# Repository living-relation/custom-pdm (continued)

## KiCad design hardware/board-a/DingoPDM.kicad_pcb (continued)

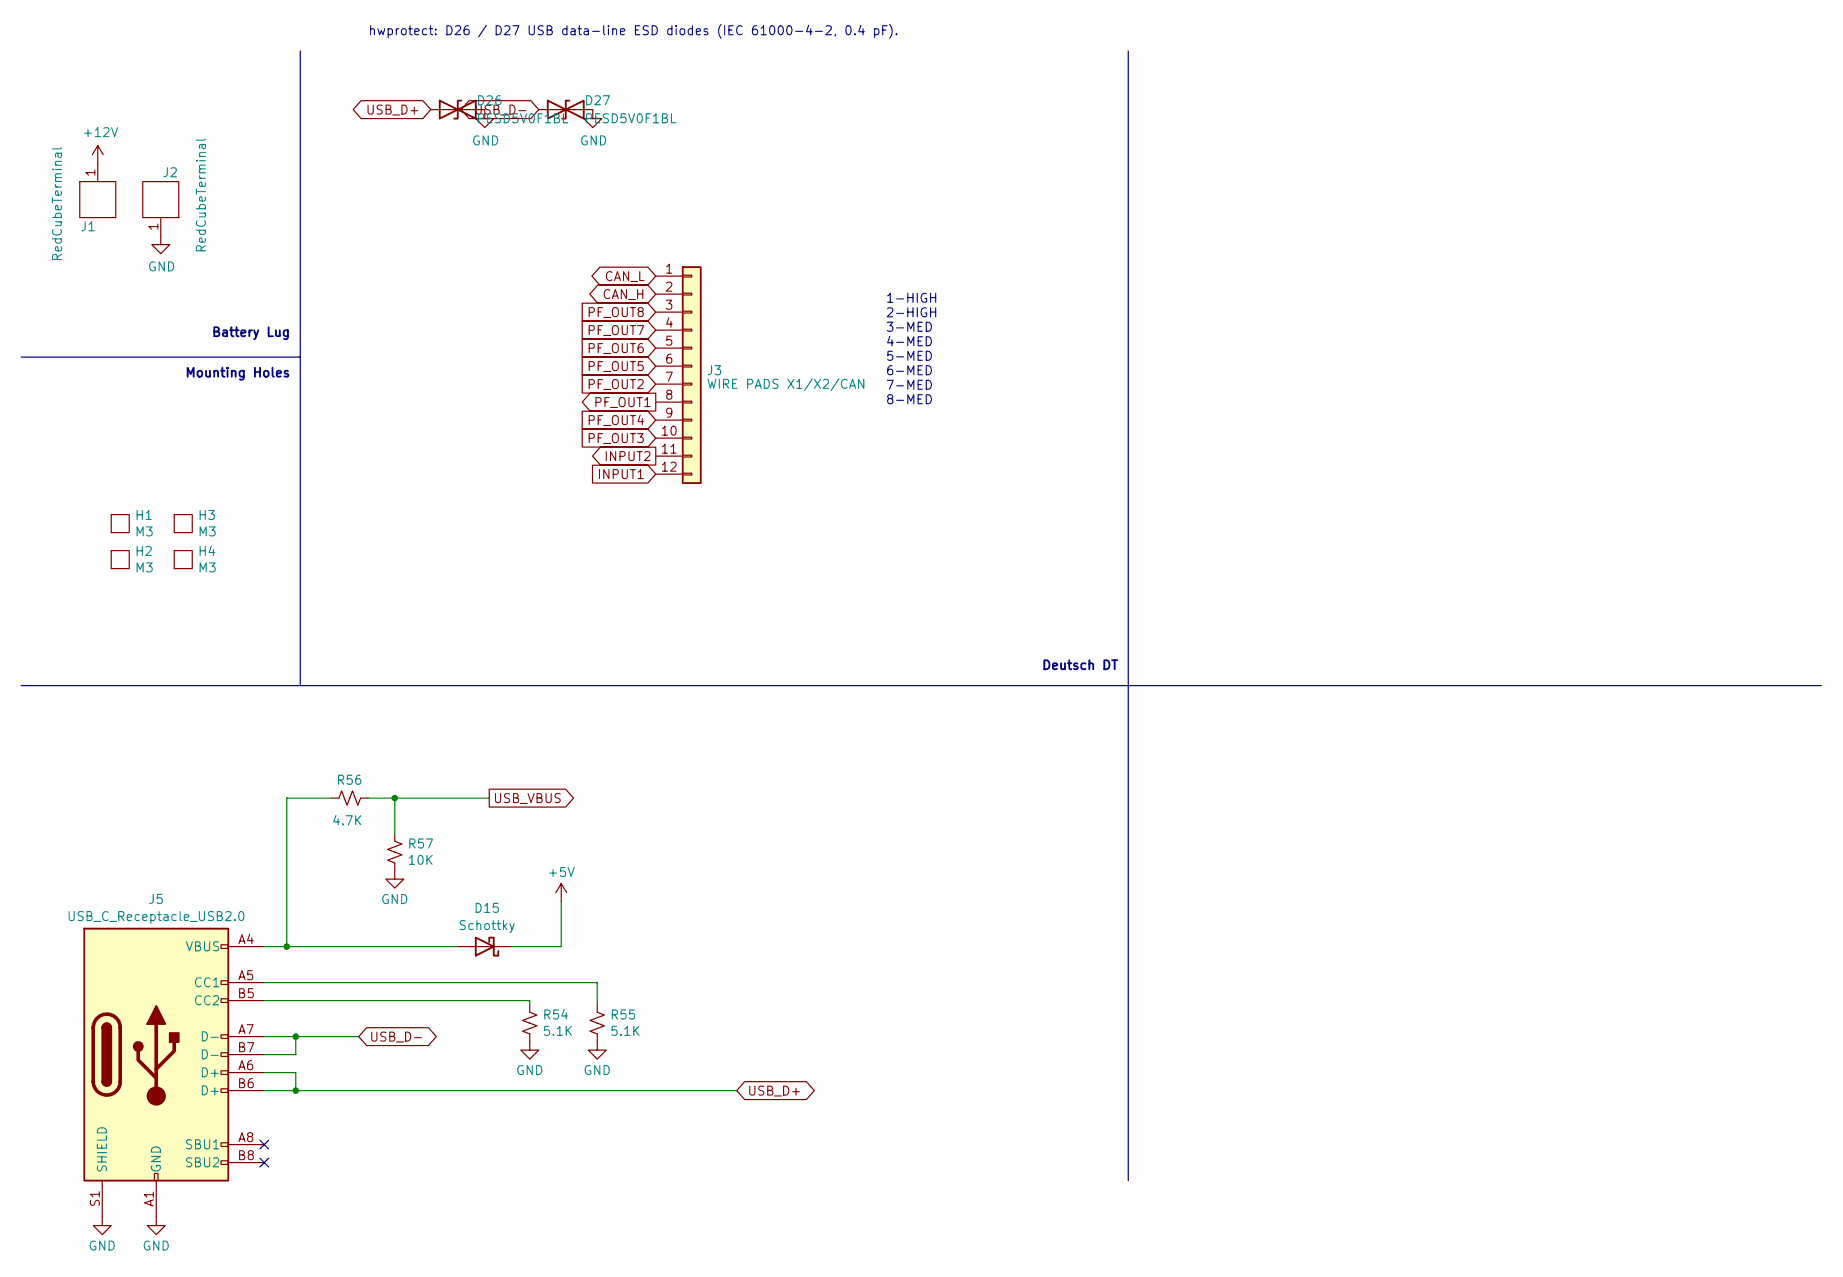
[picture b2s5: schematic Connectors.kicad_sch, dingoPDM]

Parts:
D15: Schottky; D_SOD-123; MPN PMEG10010ELRX; Digi-Key_PN 1727-2394-1-ND
D26, D27: PESD5V0F1BL; D_SOD-882; MPN PESD5V0F1BL,315; LCSC C45961
H1, H2, H3, H4: M3; MountingHole_3.2mm_M3_ISO7380_Pad
J1, J2: RedCubeTerminal; M6_Hole_8Pin_7461084; MPN 7461084; Digi-Key_PN 732-3203-ND
J3: WIRE PADS X1/X2/CAN; DT15-12PA_WirePads
J5: USB_C_Receptacle_USB2.0; USB_C_Receptacle_GCT_USB4085; MPN USB4085-GF-A; Digi-Key_PN 2073-USB4085-GF-ACT-ND
R54, R55: 5.1K; R_0805_2012Metric; MPN ARG05FTC5101; Digi-Key_PN 311-5.1KARCT-ND
R56: 4.7K; R_0805_2012Metric; MPN 0805W8F4701T5E; Digi-Key_PN 311-4.70KCRCT-ND
R57: 10K; R_0805_2012Metric; MPN 0805W8F1002T5E; Digi-Key_PN 311-10.0KCRDKR-ND

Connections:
+5V: D15.1 (K); also elsewhere on the board
+12V: J1.1; also elsewhere on the board
CAN_H: J3.2; also elsewhere on the board
CAN_L: J3.1; also elsewhere on the board
GND: D26.2 (A2), D27.2 (A2), J2.1, J5.A1 (GND), J5.A12 (GND), J5.B1 (GND), J5.B12 (GND), J5.S1 (SHIELD), R54.2, R55.2, R57.2; also elsewhere on the board
INPUT1: J3.12; also elsewhere on the board
INPUT2: J3.11; also elsewhere on the board
unnamed: D15.2 (A), J5.A4 (VBUS), J5.A9 (VBUS), J5.B4 (VBUS), J5.B9 (VBUS), R56.1
unnamed: J5.A5 (CC1), R55.1
unnamed: J5.B5 (CC2), R54.1
PF_OUT1: J3.8; also elsewhere on the board
PF_OUT2: J3.7; also elsewhere on the board
PF_OUT3: J3.10; also elsewhere on the board
PF_OUT4: J3.9; also elsewhere on the board
PF_OUT5: J3.6; also elsewhere on the board
PF_OUT6: J3.5; also elsewhere on the board
PF_OUT7: J3.4; also elsewhere on the board
PF_OUT8: J3.3; also elsewhere on the board
USB_D+: D26.1 (A1), J5.A6 (D+), J5.B6 (D+); also elsewhere on the board
USB_D-: D27.1 (A1), J5.A7 (D-), J5.B7 (D-); also elsewhere on the board
USB_VBUS: R56.2, R57.1; also elsewhere on the board

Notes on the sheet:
1-HIGH 2-HIGH 3-MED 4-MED 5-MED 6-MED 7-MED 8-MED
Deutsch DT
Battery Lug
Mounting Holes
hwprotect: D26 / D27 USB data-line ESD diodes (IEC 61000-4-2, 0.4 pF).

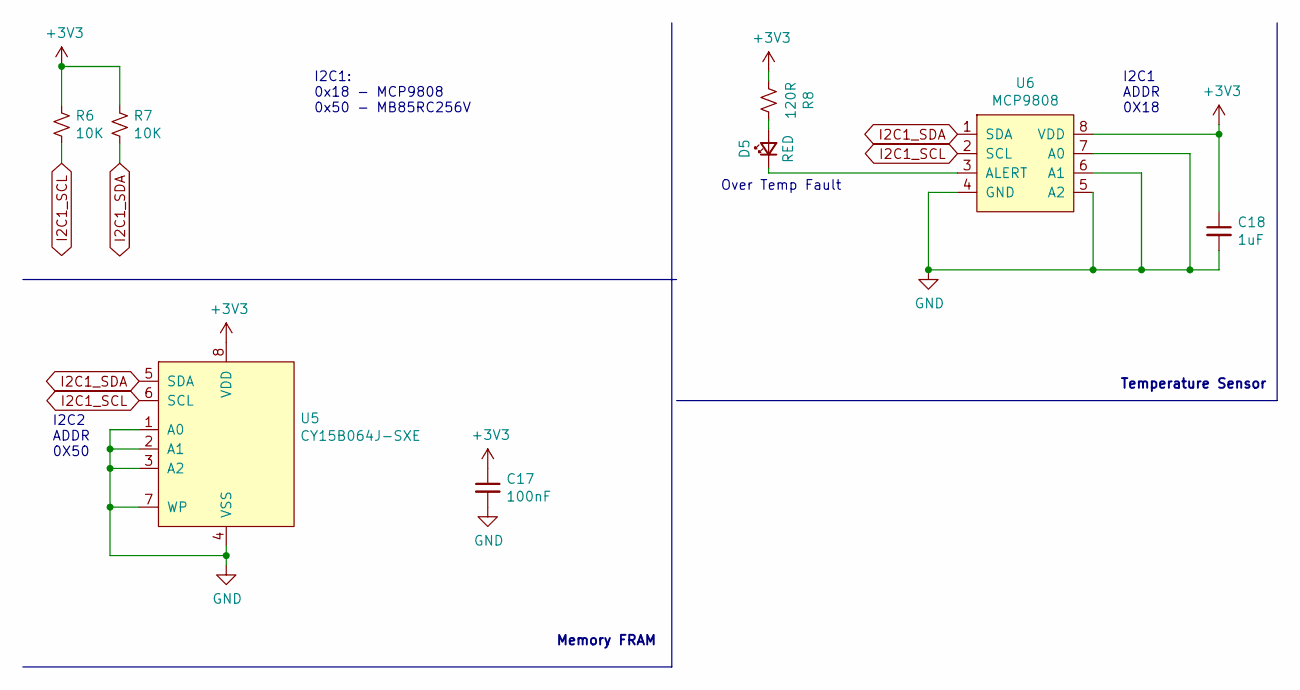
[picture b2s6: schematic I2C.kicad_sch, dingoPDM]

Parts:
C17: 100nF; C_0805_2012Metric; MPN CC0805KRX7R9BB104; Digi-Key_PN 478-1395-1-ND
C18: 1uF; C_0805_2012Metric; MPN CL21B105KBFNNNE; Digi-Key_PN 311-1365-1-ND
D5: RED; LED_0805_2012Metric; MPN LS R976-NR-1-0-20-R18; Digi-Key_PN 475-1278-1-ND
R6, R7: 10K; R_0805_2012Metric; MPN 0805W8F1002T5E; Digi-Key_PN 311-10.0KCRDKR-ND
R8: 120R; R_0805_2012Metric; MPN 0805W8F1200T5E; Digi-Key_PN 311-120CRCT-ND
U5: CY15B064J-SXE; SOIC-8_3.9x4.9mm_P1.27mm; MPN CY15B064J-SXE; Digi-Key_PN 448-CY15B064J-SXE-ND
U6: MCP9808; MSOP-8_3x3mm_P0.65mm; MPN MCP9808T-E/MS; Digi-Key_PN MCP9808T-E/MSCT-ND

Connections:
+3V3: C17.1, C18.1, R6.1, R7.1, R8.2, U5.8 (VDD), U6.8 (VDD); also elsewhere on the board
GND: C17.2, C18.2, U5.1 (A0), U5.2 (A1), U5.3 (A2), U5.4 (VSS), U5.7 (WP), U6.4 (GND), U6.5 (A2), U6.6 (A1), U6.7 (A0); also elsewhere on the board
I2C1_SCL: R6.2, U5.6 (SCL), U6.2 (SCL); also elsewhere on the board
I2C1_SDA: R7.2, U5.5 (SDA), U6.1 (SDA); also elsewhere on the board
unnamed: D5.2 (A), R8.1
unnamed: D5.1 (K), U6.3 (ALERT)

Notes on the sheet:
I2C1 ADDR 0X18
I2C2 ADDR 0X50
Over Temp Fault
Temperature Sensor
I2C1: 0x18 - MCP9808 0x50 - MB85RC256V
Memory FRAM

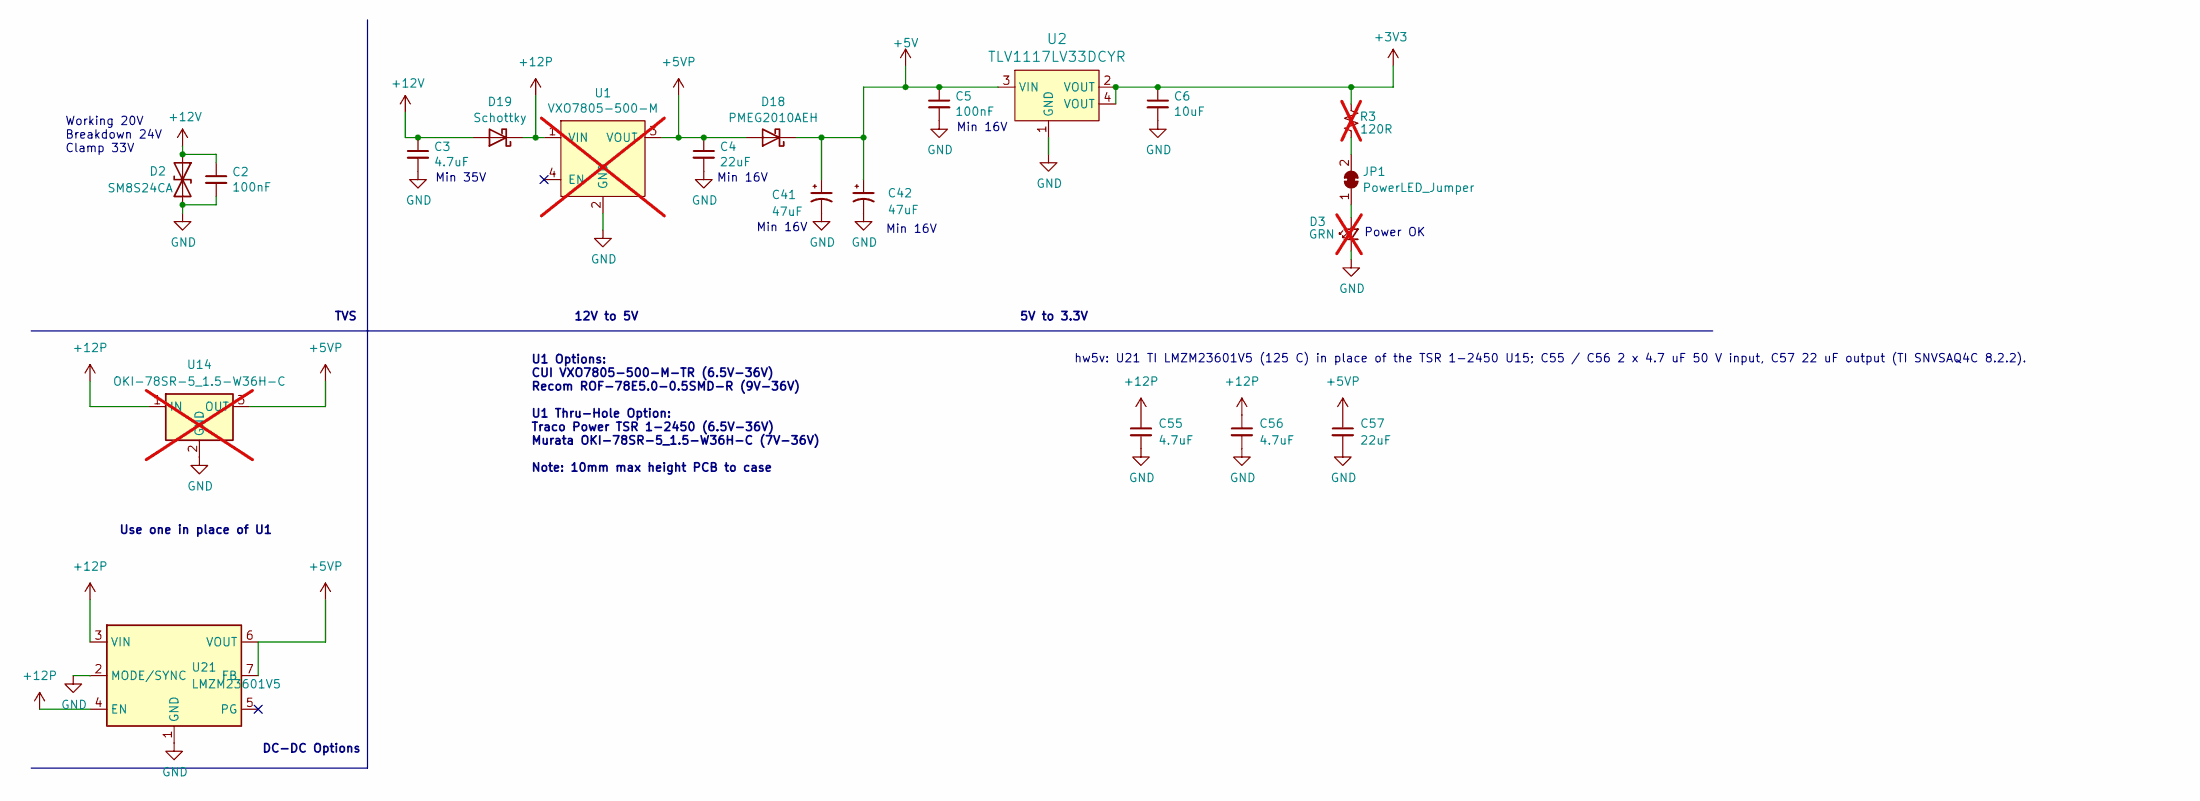
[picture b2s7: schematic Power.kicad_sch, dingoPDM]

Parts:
C2, C5: 100nF; C_0805_2012Metric; MPN CC0805KRX7R9BB104; Digi-Key_PN 478-1395-1-ND
C3, C55, C56: 4.7uF; C_0805_2012Metric; MPN CGA4J1X7R1H475KT0Y0N; LCSC C694229
C4, C57: 22uF; C_0805_2012Metric; MPN GRM21BZ71A226ME15L; LCSC C907991
C6: 10uF; C_0805_2012Metric; MPN CL21B106KPQNNNE; LCSC C32635
C41, C42: 47uF; C_2220_5750Metric; MPN FS55X476K250LRG; Digi-Key_PN 445-7935-1-ND
D2: SM8S24CA; D_DO-218AB_Vishay_SM8S; MPN SM8S24CA-Q; Digi-Key_PN SM8S24CA-QCT-ND
D3: GRN; LED_0805_2012Metric; MPN LG R971-KN-1-0-20-R18; Digi-Key_PN 475-1410-1-ND; not fitted
D18: PMEG2010AEH; D_SOD-123F; MPN PMEG2010AEH,115; Digi-Key_PN 1727-PMEG2010AEH,115CT-ND
D19: Schottky; D_SOD-123; MPN PMEG10010ELRX; Digi-Key_PN 1727-2394-1-ND
JP1: PowerLED_Jumper; SolderJumper-2_P1.3mm_Bridged_RoundedPad1.0x1.5mm
R3: 120R; R_0805_2012Metric; MPN 0805W8F1200T5E; Digi-Key_PN 311-120CRCT-ND; not fitted
U1: VXO7805-500-M; VXO78x-500-M; MPN VXO7805-500-M-TR; Digi-Key_PN 102-VXO7805-500-M-CT-ND; not fitted
U2: TLV1117LV33DCYR; SOT-223; MPN TLV1117LV33DCYR; Digi-Key_PN 296-28778-1-ND
U14: OKI-78SR-5_1.5-W36H-C; Converter_DCDC_Murata_OKI-78SR_Horizontal; MPN OKI-78SR-5/1.5-W36H-C; Digi-Key_PN 811-2692-ND; not fitted
U21: LMZM23601V5; Texas_SIL0010A_MicroSiP-10-1EP_3.8x3mm_P0.6mm_EP0.7x2.9mm_TI; MPN LMZM23601V5SILR; LCSC C2868357

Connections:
+3V3: C6.1, R3.2, U2.2 (VOUT), U2.4 (VOUT); also elsewhere on the board
+5V: C5.1, C41.1, C42.1, D18.1 (K), U2.3 (VIN); also elsewhere on the board
+5VP: C4.1, C57.1, D18.2 (A), U1.3 (VOUT), U14.3 (OUT), U21.6 (VOUT), U21.7 (FB)
+12P: C55.1, C56.1, D19.1 (K), U1.1 (VIN), U14.1 (IN), U21.3 (VIN), U21.4 (EN)
+12V: C2.1, C3.1, D2.1 (A1), D19.2 (A); also elsewhere on the board
GND: C2.2, C3.2, C4.2, C5.2, C6.2, C41.2, C42.2, C55.2, C56.2, C57.2, D2.2 (A2), D3.1 (K), U1.2 (GND), U2.1 (GND), U14.2 (GND), U21.1 (GND), U21.2 (MODE/SYNC), U21.11 (GND); also elsewhere on the board
unnamed: D3.2 (A), JP1.1 (A)
unnamed: JP1.2 (B), R3.1

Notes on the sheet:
Min 16V
TVS
Min 35V
Power OK
5V to 3.3V
U1 Options: CUI VXO7805-500-M-TR (6.5V-36V) Recom ROF-78E5.0-0.5SMD-R (9V-36V) U1 Thru-Hole Option: Traco Power TSR 1-2450 (6.5V-36V) Murata OKI-78SR-5_1.5-W36H-C (7V-36V) Note: 10mm max height PCB to case
12V to 5V
DC-DC Options
Use one in place of U1
Working 20V Breakdown 24V Clamp 33V
hw5v: U21 TI LMZM23601V5 (125 C) in place of the TSR 1-2450 U15; C55 / C56 2 x 4.7 uF 50 V input, C57 22 uF output (TI SNVSAQ4C 8.2.2).

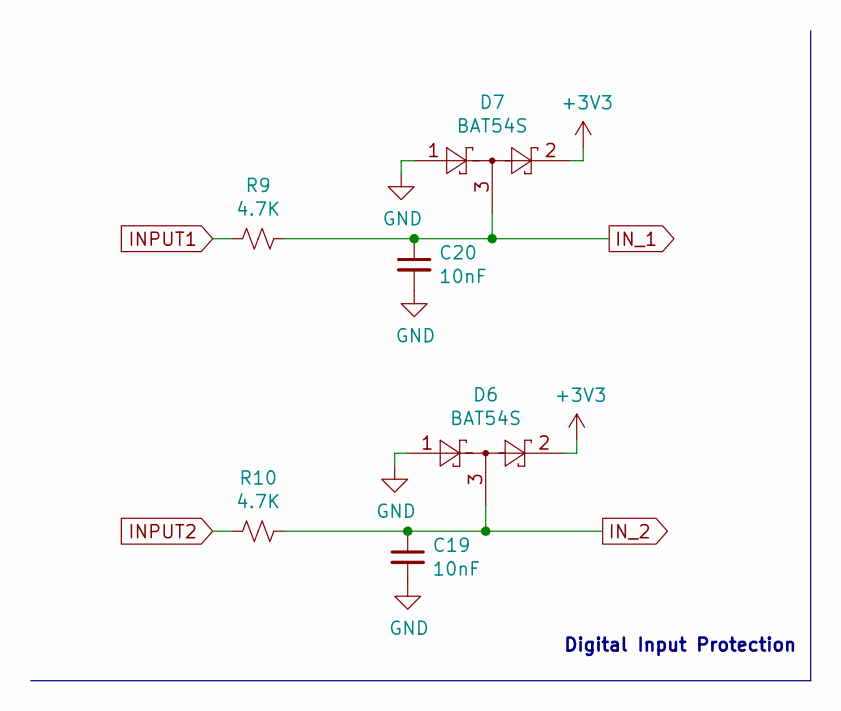
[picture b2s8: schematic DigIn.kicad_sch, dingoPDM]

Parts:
C19, C20: 10nF; C_0805_2012Metric; MPN CL21B103KBANNNC; Digi-Key_PN 311-1136-1-ND
D6, D7: BAT54S; SOT-23; MPN BAT54S,215; Digi-Key_PN BAT54SLT1GOSCT-ND
R9, R10: 4.7K; R_0805_2012Metric; MPN 0805W8F4701T5E; Digi-Key_PN 311-4.70KCRCT-ND

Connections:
+3V3: D6.2, D7.2; also elsewhere on the board
GND: C19.2, C20.2, D6.1, D7.1; also elsewhere on the board
INPUT1: R9.2; also elsewhere on the board
INPUT2: R10.2; also elsewhere on the board
IN_1: C20.1, D7.3, R9.1; also elsewhere on the board
IN_2: C19.1, D6.3, R10.1; also elsewhere on the board

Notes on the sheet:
Digital Input Protection

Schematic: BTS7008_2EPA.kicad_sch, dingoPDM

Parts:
C10: 47nF; C_0805_2012Metric; MPN C0805C473K5RAC7800; Digi-Key_PN 399-C0805C473K5RACTUCT-ND
C33: 100nF; C_0805_2012Metric; MPN CC0805KRX7R9BB104; Digi-Key_PN 478-1395-1-ND
C34: 220pF; C_0805_2012Metric; MPN CC0805GRNPO0BN221; Digi-Key_PN 399-1138-1-ND
D13: 5.1V; D_SOD-323_HandSoldering; MPN PDZ5.1B,115; Digi-Key_PN 1727-5155-1-ND
R34, R35, R36, R37, R40, R41: 4.7K; R_0805_2012Metric; MPN 0805W8F4701T5E; Digi-Key_PN 311-4.70KCRCT-ND
R38: 1.2K; R_0805_2012Metric; MPN 0805W8F1201T5E; Digi-Key_PN 311-1.20KCRCT-ND
R39: 47R 1/4W; R_1206_3216Metric; MPN FRC1206J470 TS; Digi-Key_PN 311-47.0FRCT-ND
U10: BTS7008-2EPA; TDSO-14; MPN BTS70082EPAXUMA1; Digi-Key_PN BTS70082EPAXUMA1CT-ND

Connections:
+12V: C10.2, C33.2, U10.15 (VS); also elsewhere on the board
/MedCurrentDrivers/Sheet5F5A9675/IS: C34.2, R41.1; also elsewhere on the board
GND: C33.1, C34.1, D13.2 (A), R38.2, R39.1; also elsewhere on the board
unnamed: D13.1 (K), R40.1, R41.2
unnamed: R35.1, U10.3 (DEN)
unnamed: R36.2, U10.5 (DSEL)
unnamed: C10.1, R39.2, U10.1 (GND)
unnamed: R34.1, U10.2 (IN0)
unnamed: R37.1, U10.6 (IN1)
unnamed: R38.1, R40.2, U10.4 (IS)
PF_DEN5_6: R35.2; also elsewhere on the board
PF_DSEL5_6: R36.1; also elsewhere on the board
PF_IN5: R34.2; also elsewhere on the board
PF_IN6: R37.2; also elsewhere on the board
PF_OUT5: U10.12 (OUT0), U10.13 (OUT0), U10.14 (OUT0); also elsewhere on the board
PF_OUT6: U10.8 (OUT1), U10.9 (OUT1), U10.10 (OUT1); also elsewhere on the board

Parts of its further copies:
C22, C30, C35: 47nF; C_0805_2012Metric; MPN C0805C473K5RAC7800; Digi-Key_PN 399-C0805C473K5RACTUCT-ND
C23, C31, C36: 100nF; C_0805_2012Metric; MPN CC0805KRX7R9BB104; Digi-Key_PN 478-1395-1-ND
C25, C32, C37: 220pF; C_0805_2012Metric; MPN CC0805GRNPO0BN221; Digi-Key_PN 399-1138-1-ND
D9, D12, D14: 5.1V; D_SOD-323_HandSoldering; MPN PDZ5.1B,115; Digi-Key_PN 1727-5155-1-ND
R13, R14, R17, R18, R19, R20, R26, R27, R28, R29, R32, R33, R43, R44, R45, R46, R49, R50: 4.7K; R_0805_2012Metric; MPN 0805W8F4701T5E; Digi-Key_PN 311-4.70KCRCT-ND
R15, R30, R47: 1.2K; R_0805_2012Metric; MPN 0805W8F1201T5E; Digi-Key_PN 311-1.20KCRCT-ND
R16, R31, R48: 47R 1/4W; R_1206_3216Metric; MPN FRC1206J470 TS; Digi-Key_PN 311-47.0FRCT-ND
U8, U11, U13: BTS7008-2EPA; TDSO-14; MPN BTS70082EPAXUMA1; Digi-Key_PN BTS70082EPAXUMA1CT-ND

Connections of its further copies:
+12V: C22.2, C23.2, C30.2, C31.2, C35.2, C36.2, U8.15 (VS), U11.15 (VS), U13.15 (VS); also elsewhere on the board
/HighCurrentDrivers/sheet5F5A40B9/IS: C25.2, R18.1; also elsewhere on the board
/MedCurrentDrivers/Sheet5F5A9674/IS: C32.2, R33.1; also elsewhere on the board
/MedCurrentDrivers/Sheet5F5A9676/IS: C37.2, R50.1; also elsewhere on the board
GND: C23.1, C25.1, C31.1, C32.1, C36.1, C37.1, D9.2 (A), D12.2 (A), D14.2 (A), R15.2, R16.1, R30.2, R31.1, R47.2, R48.1; also elsewhere on the board
unnamed: D9.1 (K), R17.1, R18.2
unnamed: D12.1 (K), R32.1, R33.2
unnamed: D14.1 (K), R49.1, R50.2
unnamed: R14.1, U8.3 (DEN)
unnamed: R20.2, U8.5 (NC1)
unnamed: C22.1, R16.2, U8.1 (GND)
unnamed: R13.1, U8.2 (IN)
unnamed: R19.1, U8.6 (NC2)
unnamed: R15.1, R17.2, U8.4 (IS)
unnamed: R27.1, U11.3 (DEN)
unnamed: R28.2, U11.5 (DSEL)
unnamed: C30.1, R31.2, U11.1 (GND)
unnamed: R26.1, U11.2 (IN0)
unnamed: R29.1, U11.6 (IN1)
unnamed: R30.1, R32.2, U11.4 (IS)
unnamed: R44.1, U13.3 (DEN)
unnamed: R45.2, U13.5 (DSEL)
unnamed: C35.1, R48.2, U13.1 (GND)
unnamed: R43.1, U13.2 (IN0)
unnamed: R46.1, U13.6 (IN1)
unnamed: R47.1, R49.2, U13.4 (IS)
PF_DEN1: R14.2; also elsewhere on the board
PF_DEN3_4: R27.2; also elsewhere on the board
PF_DEN7_8: R44.2; also elsewhere on the board
PF_DSEL1_2: R20.1; also elsewhere on the board
PF_DSEL3_4: R28.1; also elsewhere on the board
PF_DSEL7_8: R45.1; also elsewhere on the board
PF_IN1: R13.2; also elsewhere on the board
PF_IN2: R19.2; also elsewhere on the board
PF_IN3: R26.2; also elsewhere on the board
PF_IN4: R29.2; also elsewhere on the board
PF_IN7: R43.2; also elsewhere on the board
PF_IN8: R46.2; also elsewhere on the board
PF_OUT1: U8.12 (OUT4), U8.13 (OUT5), U8.14 (OUT6); also elsewhere on the board
PF_OUT2: U8.8 (OUT1), U8.9 (OUT2), U8.10 (OUT3); also elsewhere on the board
PF_OUT3: U11.12 (OUT0), U11.13 (OUT0), U11.14 (OUT0); also elsewhere on the board
PF_OUT4: U11.8 (OUT1), U11.9 (OUT1), U11.10 (OUT1); also elsewhere on the board
PF_OUT7: U13.12 (OUT0), U13.13 (OUT0), U13.14 (OUT0); also elsewhere on the board
PF_OUT8: U13.8 (OUT1), U13.9 (OUT1), U13.10 (OUT1); also elsewhere on the board

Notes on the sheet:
RC Filter

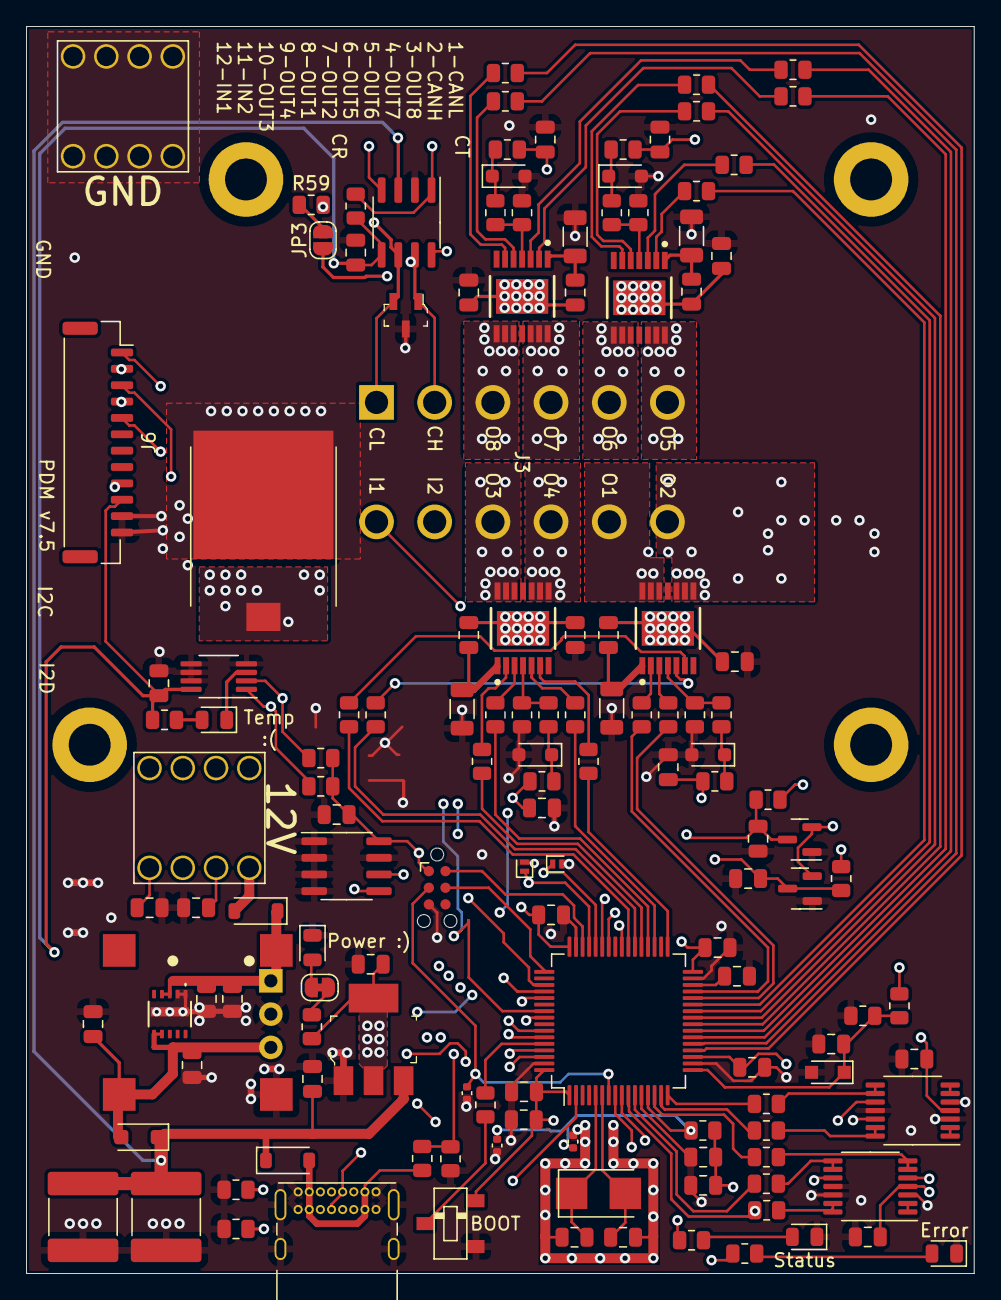
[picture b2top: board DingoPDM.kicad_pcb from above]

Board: 4 copper layers, 72.4 x 95.2 mm, 145 parts (1 on the bottom side), 116 nets.

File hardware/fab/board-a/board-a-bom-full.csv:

Qty,Designator,Value,Footprint,Manufacturer,MPN,LCSC,Digi-Key,Approved alternates,Fitted by
16,"C1,C2,C5,C9,C11,C12,C13,C15,C17,C21,C23,C31,C33,C36,C39,C40",100nF,C_0805_2012Metric,YAGEO,CC0805KRX7R9BB104,C49678,478-1395-1-ND,,JLCPCB SMT
3,"C3,C55,C56",4.7uF,C_0805_2012Metric,TDK,CGA4J1X7R1H475KT0Y0N,C694229,,"HRE CGA0805X7R475K500MT (4.7 uF 50 V X7R 0805, LCSC C6119944)",JLCPCB SMT
2,"C4,C57",22uF,C_0805_2012Metric,Murata,GRM21BZ71A226ME15L,C907991,,"CCTC TCC0805X7R226M100FT (22 uF 10 V X7R 0805, LCSC C53133025)",JLCPCB SMT
1,C6,10uF,C_0805_2012Metric,Samsung Electro-Mechanics,CL21B106KPQNNNE,C32635,,,JLCPCB SMT
2,"C7,C8",27pF,C_0805_2012Metric,FH (Guangdong Fenghua),0805CG270J500NT,C1808,478-10518-1-ND,,JLCPCB SMT
4,"C10,C22,C30,C35",47nF,C_0805_2012Metric,KEMET,C0805C473K5RAC7800,C3879816,399-C0805C473K5RACTUCT-ND,"KEMET C0805C473K5RACTU (same part, other reel code; DK 399-C0805C473K5RACTUCT-ND)",JLCPCB SMT
2,"C14,C38",4.7uF,C_0805_2012Metric,Samsung Electro-Mechanics,CL21B475KAFNNNE,C98195,,,JLCPCB SMT
2,"C16,C18",1uF,C_0805_2012Metric,Samsung Electro-Mechanics,CL21B105KBFNNNE,C28323,311-1365-1-ND,,JLCPCB SMT
2,"C19,C20",10nF,C_0805_2012Metric,Samsung Electro-Mechanics,CL21B103KBANNNC,C1710,311-1136-1-ND,,JLCPCB SMT
4,"C25,C32,C34,C37",220pF,C_0805_2012Metric,YAGEO,CC0805GRNPO0BN221,C576920,399-1138-1-ND,,JLCPCB SMT
2,"C41,C42",47uF,C_2220_5750Metric,PSA,FS55X476K250LRG,C22388555,445-7935-1-ND,,JLCPCB SMT
2,"C52,C54",100nF,C_0402_1005Metric,Samsung Electro-Mechanics,CL05B104KO5NNNC,C1525,,YAGEO CC0402KRX7R7BB104 (X7R 16 V 0402),JLCPCB SMT
1,C53,1uF,C_0402_1005Metric,CCTC,TCC0402X7R105K100AT,C47325373,,"YAGEO CC0402KRX7R6BB105 (X7R 10 V 0402, LCSC C7500381)",JLCPCB SMT
1,D1,3.3V,D_SOD-323_HandSoldering,Nexperia,"PDZ3.3B,115",C426855,1727-5150-1-ND,,JLCPCB SMT
1,D2,SM8S24CA,D_DO-218AB_Vishay_SM8S,Bourns,SM8S24CA-Q,C1976790,SM8S24CA-QCT-ND,"Vishay SM8S24CAHM3/I (LCSC C20036943, DK 112-SM8S24CAHM3/ITR-ND); Panjit SM8H24CAS-AU",JLCPCB SMT
1,D3,GRN,LED_0805_2012Metric,OSRAM,LG R971-KN-1-0-20-R18,C2899888,475-1410-1-ND,,do not fit
1,D4,NUP2105LT1G,SOT-23-3,DOWO,NUP2105LT1G,C2976509,NUP2105LT1GOSCT-ND,onsemi NUP2105LT1G (DK NUP2105LT1GOSCT-ND),JLCPCB SMT
2,"D5,D16",RED,LED_0805_2012Metric,OSRAM,LS R976-NR-1-0-20-R18,C2899997,475-1278-1-ND,,JLCPCB SMT
2,"D6,D7",BAT54S,SOT-23,Nexperia,"BAT54S,215",C47546,BAT54SLT1GOSCT-ND,onsemi BAT54SLT1G (DK BAT54SLT1GOSCT-ND),JLCPCB SMT
4,"D9,D12,D13,D14",5.1V,D_SOD-323_HandSoldering,Nexperia,"PDZ5.1B,115",C85392,1727-5155-1-ND,,JLCPCB SMT
2,"D15,D19",Schottky,D_SOD-123,Nexperia,PMEG10010ELRX,C179426,1727-2394-1-ND,,JLCPCB SMT
1,D17,GRN,LED_0805_2012Metric,OSRAM,LG R971-KN-1-0-20-R18,C2899888,475-1410-1-ND,,JLCPCB SMT
1,D18,PMEG2010AEH,D_SOD-123F,Nexperia,"PMEG2010AEH,115",C110921,"1727-PMEG2010AEH,115CT-ND",,JLCPCB SMT
2,"D26,D27",PESD5V0F1BL,D_SOD-882,Nexperia,"PESD5V0F1BL,315",C45961,,Nexperia PESD5V0F1BLZ (LCSC C6952437); BORN PESD5V0F1BL-N (LCSC C2929237),JLCPCB SMT
1,FB1,Ferrite_Bead_Small,R_0805_2012Metric,Murata,BLM21PG221SN1D,C85840,490-1054-1-ND,,JLCPCB SMT
2,"J1,J2",RedCubeTerminal,M6_Hole_8Pin_7461084,Wurth Elektronik,7461084,C6828431,732-3203-ND,,not JLCPCB: press in after delivery (fab-notes.md)
1,J5,USB_C_Receptacle_USB2.0,USB_C_Receptacle_GCT_USB4085,GCT,USB4085-GF-A,C7095263,2073-USB4085-GF-ACT-ND,,JLCPCB THT
1,J6,INPUTS IN3-IN10,JST_GH_SM12B-GHS-TB_1x12-1MP_P1.25mm_Horizontal,JST,SM12B-GHS-TB(LF)(SN),C265421,455-1574-1-ND,,JLCPCB SMT
1,R1,47K,R_0805_2012Metric,YAGEO,RT0805DRD0747KL,C327035,311-47.0KCRCT-ND,"UNI-ROYAL 0805W8F4702T5E (1 %, LCSC C17713, basic)",JLCPCB SMT
28,"R2,R9,R10,R13,R14,R17,R18,R19,R20,R26,R27,R28,R29,R32,R33,R34,R35,R36,R37,R40,R41,R43,R44,R45,R46,R49,R50,R56",4.7K,R_0805_2012Metric,UNI-ROYAL,0805W8F4701T5E,C17673,311-4.70KCRCT-ND,,JLCPCB SMT
2,"R3,R12",120R,R_0805_2012Metric,UNI-ROYAL,0805W8F1200T5E,C17437,311-120CRCT-ND,YAGEO RC0805FR-07120RL (DK 311-120CRCT-ND),do not fit
4,"R4,R6,R7,R57",10K,R_0805_2012Metric,UNI-ROYAL,0805W8F1002T5E,C17414,311-10.0KCRDKR-ND,,JLCPCB SMT
1,R5,1K,R_0805_2012Metric,UNI-ROYAL,0805W8F1001T5E,C17513,311-1.0KARCT-ND,,JLCPCB SMT
8,"R8,R11,R25,R42,R51,R52,R53,R59",120R,R_0805_2012Metric,UNI-ROYAL,0805W8F1200T5E,C17437,311-120CRCT-ND,YAGEO RC0805FR-07120RL (DK 311-120CRCT-ND),JLCPCB SMT
4,"R15,R30,R38,R47",1.2K,R_0805_2012Metric,UNI-ROYAL,0805W8F1201T5E,C17379,311-1.20KCRCT-ND,YAGEO RC0805FR-071K2L (DK 311-1.20KCRCT-ND),JLCPCB SMT
4,"R16,R31,R39,R48",47R 1/4W,R_1206_3216Metric,FOJAN,FRC1206J470 TS,C2907508,311-47.0FRCT-ND,,JLCPCB SMT
2,"R54,R55",5.1K,R_0805_2012Metric,Viking,ARG05FTC5101,C218638,311-5.1KARCT-ND,,JLCPCB SMT
1,SW1,BOOT,CJS-1200TB,Nidec Components,CJS-1200TB1,C2921631,563-CJS-1200TB1CT-ND,,JLCPCB SMT
1,U1,VXO7805-500-M,VXO78x-500-M,CUI,VXO7805-500-M-TR,C5137464,102-VXO7805-500-M-CT-ND,,do not fit
1,U2,TLV1117LV33DCYR,SOT-223,Texas Instruments,TLV1117LV33DCYR,C15578,296-28778-1-ND,,JLCPCB SMT
1,U3,MCP2562FD-E/SN,SOIC-8_3.9x4.9mm_P1.27mm,Microchip,MCP2562FD-E/SN,C124016,MCP2562FD-E/SN-ND,,JLCPCB SMT
1,U4,STM32F446RET7,LQFP-64_10x10mm_P0.5mm,STMicroelectronics,STM32F446RET7,C1343794,497-16775-ND,STMicroelectronics STM32F446RET6 (s9a; LCSC C69336),JLCPCB SMT
1,U5,CY15B064J-SXE,SOIC-8_3.9x4.9mm_P1.27mm,Infineon,CY15B064J-SXE,C2953601,448-CY15B064J-SXE-ND,"RAMXEED MB85RC64TAPNF-G-AWERE2 (LCSC C43379785; 105 C part: fit only with the board's critical limit keeping the FRAM <= 105 C, docs/heat-analysis.md 5)",JLCPCB SMT
1,U6,MCP9808,MSOP-8_3x3mm_P0.65mm,Microchip,MCP9808T-E/MS,C129490,MCP9808T-E/MSCT-ND,,JLCPCB SMT
2,"U7,U12",TLV9004IPWR,TSSOP-14_4.4x5mm_P0.65mm,Texas Instruments,TLV9004IPWR,C2058050,296-51827-1-ND,"Microchip MCP6004T-E/ST (RRIO, -40 to 125 C, same TSSOP-14 pinout, DS20001733)",JLCPCB SMT
4,"U8,U10,U11,U13",BTS7008-2EPA,TDSO-14,Infineon,BTS70082EPAXUMA1,C2150060,BTS70082EPAXUMA1CT-ND,"Infineon BTS7008-2EPA (same chip, LCSC C534830)",JLCPCB SMT
1,U14,OKI-78SR-5_1.5-W36H-C,Converter_DCDC_Murata_OKI-78SR_Horizontal,Murata,OKI-78SR-5/1.5-W36H-C,C266374,811-2692-ND,,do not fit
1,U21,LMZM23601V5,Texas_SIL0010A_MicroSiP-10-1EP_3.8x3mm_P0.6mm_EP0.7x2.9mm_TI,Texas Instruments,LMZM23601V5SILR,C2868357,296-LMZM23601V5SILRCT-ND,"TI LMZM23601V5SILT (same part, 250 reel, LCSC C2876787)",JLCPCB SMT
1,Y1,8MHz,Crystal_SMD_5032-2Pin_5.0x3.2mm_HandSoldering,ECS Inc.,ECS-80-18-30Q-CES-TR,(none: JLCPCB global sourcing by MPN),50-ECS-80-18-30Q-CES-TRCT-ND,"ECS ECS-80-18-30Q-VY-TR (-40..105 C, LCSC C6844210)",JLCPCB SMT

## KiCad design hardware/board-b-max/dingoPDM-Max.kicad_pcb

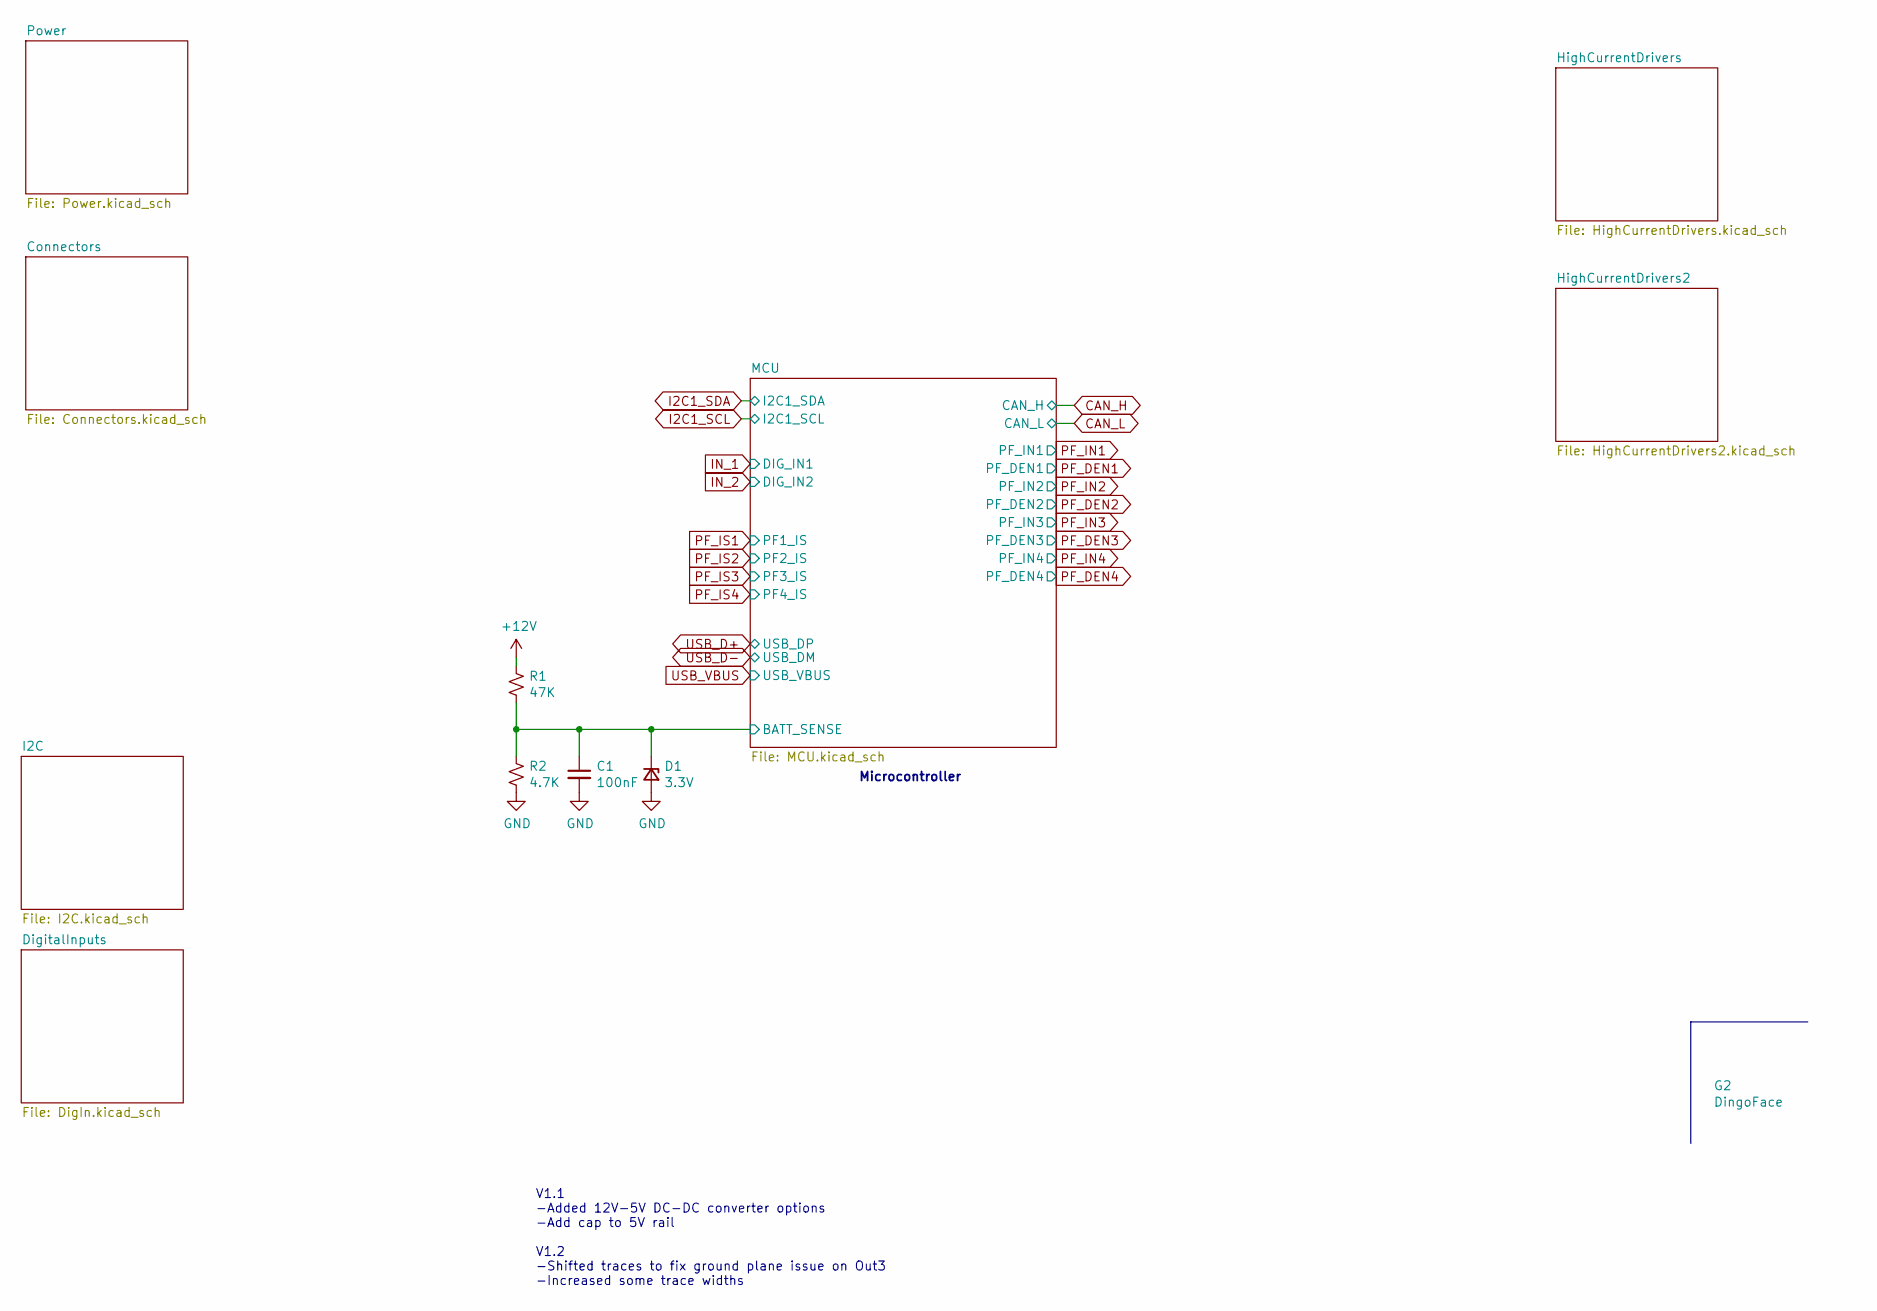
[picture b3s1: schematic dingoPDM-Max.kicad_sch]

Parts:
C1: 100nF; C_0805_2012Metric; MPN CC0805KRX7R9BB104; Digi-Key_PN 478-1395-1-ND
D1: 3.3V; D_SOD-323_HandSoldering; MPN PDZ3.3B,115; Digi-Key_PN 1727-5150-1-ND
G2: DingoFace; DingoFaceNoFill
R1: 47K; R_0805_2012Metric; MPN RT0805DRD0747KL; Digi-Key_PN 311-47.0KCRCT-ND
R2: 4.7K; R_0805_2012Metric; MPN 0805W8F4701T5E; Digi-Key_PN 311-4.70KCRCT-ND

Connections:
+12V: R1.1; also elsewhere on the board
/MCU/BATT_SENSE: C1.1, D1.1 (K), R1.2, R2.1; also elsewhere on the board
GND: C1.2, D1.2 (A), R2.2; also elsewhere on the board

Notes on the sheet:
Microcontroller
V1.1 -Added 12V-5V DC-DC converter options -Add cap to 5V rail V1.2 -Shifted traces to fix ground plane issue on Out3 -Increased some trace widths
